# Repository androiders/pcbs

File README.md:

View this project on [CADLAB.io](https://cadlab.io/project/1457). 

# pcbs
Repo for pcb layouts, gerber and gcode files

## Ki-Cad

### PCB layout:
* Use as wide traces as possible. 1mm preffered.
* Dont use "filled areas" if possible. It does not make good geometry in flatcam
* Don't forget to set origin marker
* Export gerber: use auxiliary axis

## FlatCam

### geometry generation:
* If you are using thru-hole components or using bottom layer, mirror around y axis for both geometry and Drilling
* Edit drill files if necessary for fewer drill sizes
* TODO: test double sided layout by mirroring around center axis!

### Isolation generation:
* Current isolation mill depth to test: 0.04 mm (0.05 was tested and seems to work fine!) (Common copper depth is about 0.03 mm)
* Current feedrate on isolation milling to test: 60 mm/s
* spindle speed 12000 rpm

* use 0.2 mm tool width on cnc generation
* 2 passes with 0.1 overlap

### Cutout generation:
* Current cutout mill depth: 1.6 mm
* Current feedrate on cutout milling: 40 mm/s
* spindle speed 12000 rpm

### FlatCam defaults:
* put a link in ~/.FlatCAM/defaults.json

## bCNC

### Probe:
* Fastfeed: 120
* Probefeed: 25
* Probe points: 4/cm (in each direction)

### Drilling:
* Current drill plunge rate to test 20 mm/s
* spindle speed: 12000 rpm
* Drill depth: 1.6

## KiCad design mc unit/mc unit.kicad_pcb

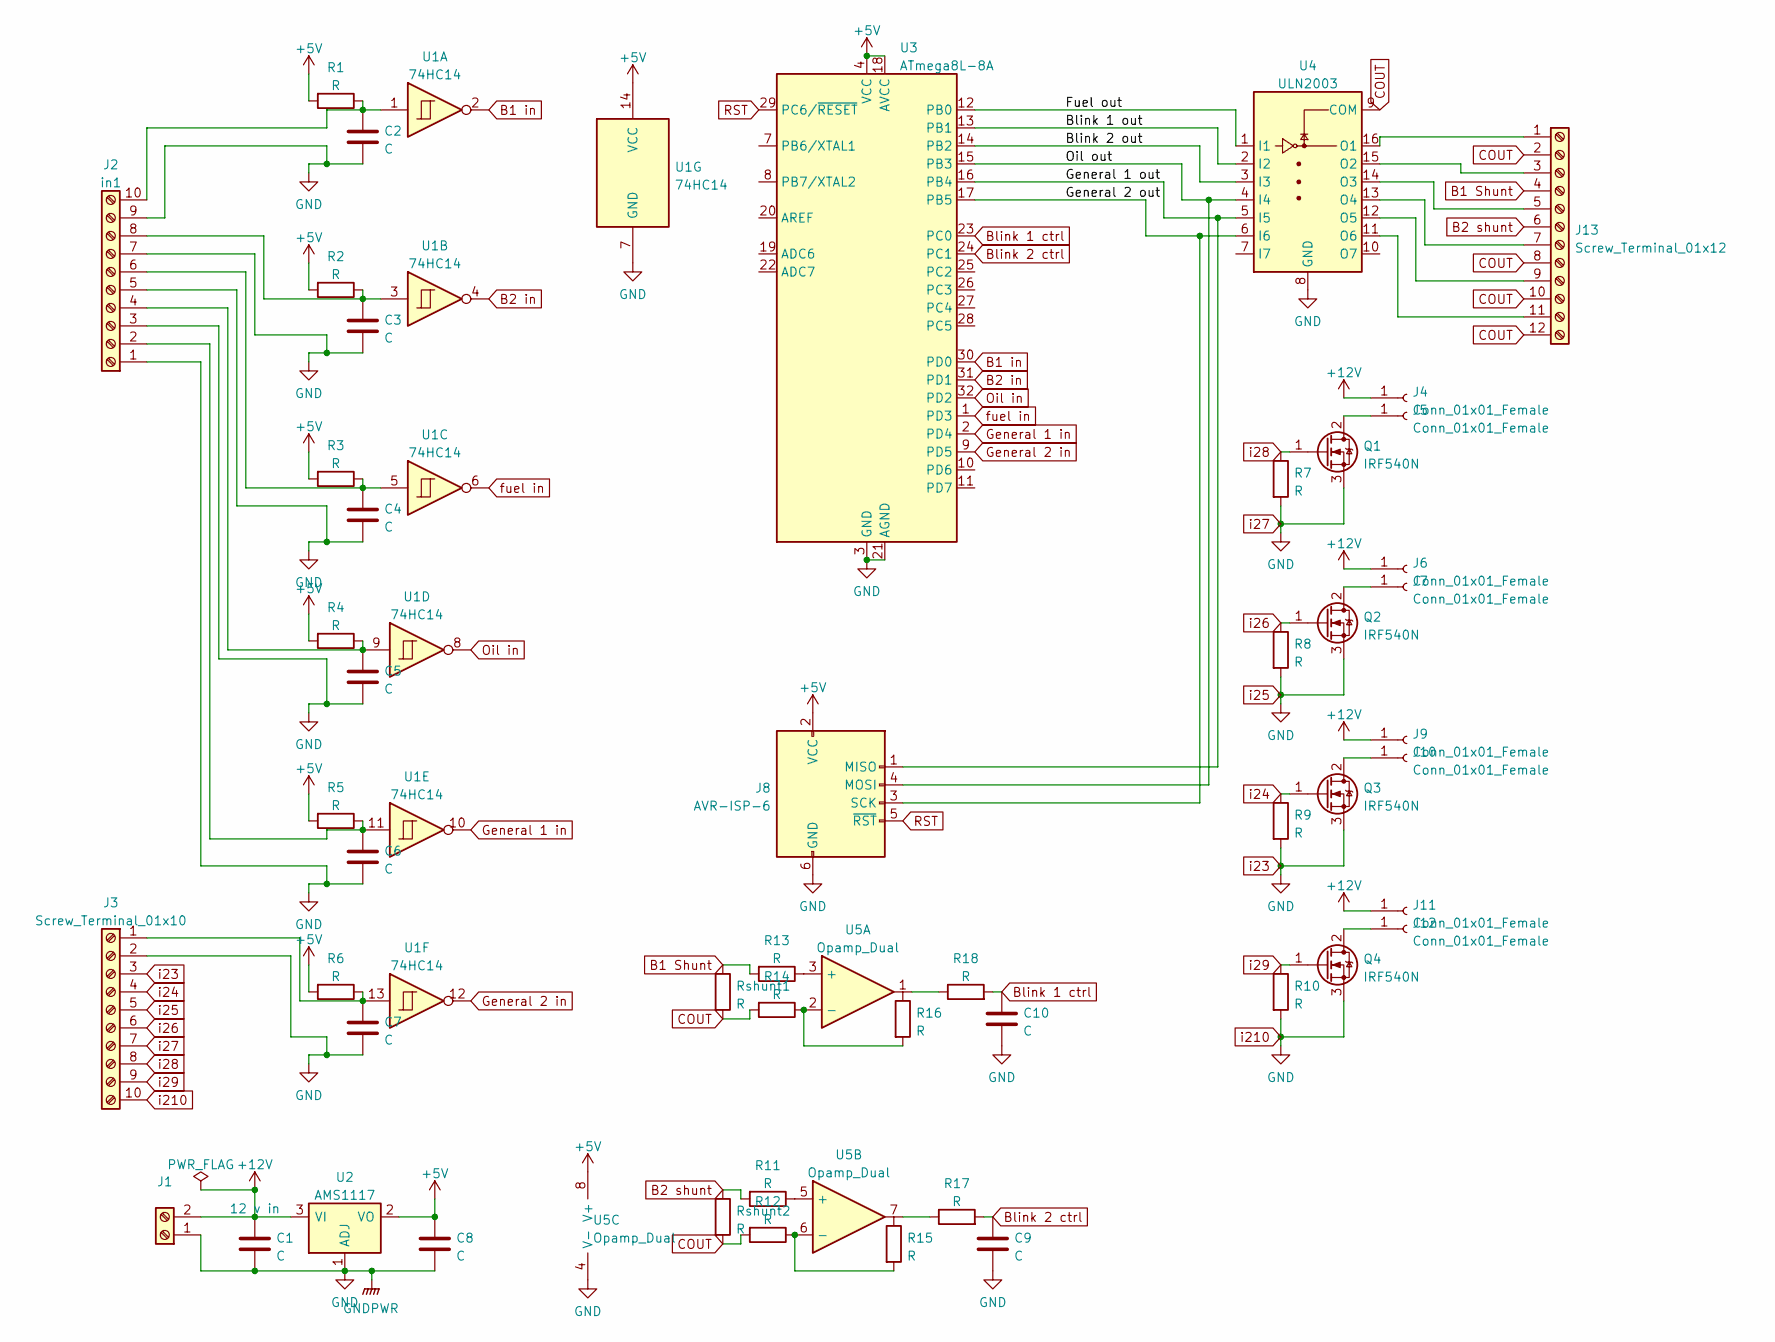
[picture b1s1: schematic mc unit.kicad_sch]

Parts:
C1, C2, C3, C4, C5, C6, C7, C8, C9, C10: C; C_1206_3216Metric
J1: 12 v in; TerminalBlock_Phoenix_MKDS-1,5-2-5.08_1x02_P5.08mm_Horizont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
J2: in1; TerminalBlock_Phoenix_MPT-0,5-10-2.54_1x10_P2.54mm_Horizont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
J3: Screw_Terminal_01x10; TerminalBlock_Phoenix_MPT-0,5-10-2.54_1x10_P2.54mm_Horizont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
J4, J5, J6, J7, J9, J10, J11, J12: Conn_01x01_Female; Pin_D1.0mm_L10.0mm_LooseFit
J8: AVR-ISP-6; IDC-Header_2x03_P2.54mm_Vertical
J13: Screw_Terminal_01x12; TerminalBlock_Phoenix_MPT-0,5-12-2.54_1x12_P2.54mm_Horizont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
Q1, Q2, Q3, Q4: IRF540N; TO-220-3_Vertical
R1, R2, R3, R4, R5, R6, R7, R8, R9, R10, R11, R12, R13, R14, R15, R16, R17, R18: R; R_1206_3216Metric
Rshunt1, Rshunt2: R; R_1206_3216Metric
U1: 74HC14; SO-14_5.3x10.2mm_P1.27mm
U2: AMS1117; SOT-223-3_TabPin2
U3: ATmega8L-8A; TQFP-32_7x7mm_P0.8mm
U4: ULN2003; SOIC-16_3.9x9.9mm_P1.27mm
U5: Opamp_Dual; SOIC-8_3.9x4.9mm_P1.27mm

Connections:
+5V: C8.1, J8.2 (VCC), R1.2, R2.2, R3.2, R4.2, R5.2, R6.2, U1.14 (VCC), U2.2 (VO), U3.4 (VCC), U3.6 (VCC), U3.18 (AVCC), U5.8 (V+)
+12V: C1.1, J1.2, J4.1, J6.1, J9.1, J11.1, U2.3 (VI)
/Blink 1 out: U3.13 (PB1), U4.2 (I2)
/Blink 2 out: U3.14 (PB2), U4.3 (I3)
/Fuel out: U3.12 (PB0), U4.1 (I1)
/General 1 out: J8.1 (MISO), U3.16 (PB4), U4.5 (I5)
/General 2 out: J8.3 (SCK), U3.17 (PB5), U4.6 (I6)
/Oil out: J8.4 (MOSI), U3.15 (PB3), U4.4 (I4)
B1 Shunt: J13.4, R13.2, Rshunt1.1
B1 in: U1.2, U3.30 (PD0)
B2 in: U1.4, U3.31 (PD1)
B2 shunt: J13.6, R11.2, Rshunt2.1
Blink 1 ctrl: C10.1, R18.2, U3.23 (PC0)
Blink 2 ctrl: C9.1, R17.2, U3.24 (PC1)
COUT: J13.2, J13.8, J13.10, J13.12, R12.2, R14.2, Rshunt1.2, Rshunt2.2, U4.9 (COM)
General 1 in: U1.10, U3.2 (PD4)
General 2 in: U1.12, U3.9 (PD5)
unnamed: C2.1, J2.10, R1.1, U1.1
unnamed: C3.1, J2.8, R2.1, U1.3
unnamed: C4.1, J2.6, R3.1, U1.5
unnamed: C5.1, J2.4, R4.1, U1.9
unnamed: C6.1, J2.2, R5.1, U1.11
unnamed: C7.1, J3.1, R6.1, U1.13
unnamed: J5.1, Q1.2 (D)
unnamed: J7.1, Q2.2 (D)
unnamed: J10.1, Q3.2 (D)
unnamed: J12.1, Q4.2 (D)
unnamed: R11.1, U5.5 (+)
unnamed: R12.1, R15.2, U5.6 (-)
unnamed: R13.1, U5.3 (+)
unnamed: R14.1, R16.2, U5.2 (-)
unnamed: R17.1, U5.7
unnamed: R18.1, U5.1
unnamed: J13.11, U4.11 (O6)
unnamed: J13.9, U4.12 (O5)
unnamed: J13.7, U4.13 (O4)
unnamed: J13.5, U4.14 (O3)
unnamed: J13.3, U4.15 (O2)
unnamed: J13.1, U4.16 (O1)
Oil in: U1.8, U3.32 (PD2)
RST: J8.5 (~RST), U3.29 (PC6/~RESET)
fuel in: U1.6, U3.1 (PD3)
i24: J3.4, Q3.1 (G), R9.1
i26: J3.6, Q2.1 (G), R8.1
i28: J3.8, Q1.1 (G), R7.1
i29: J3.9, Q4.1 (G), R10.1
i210: C1.2, C2.2, C3.2, C4.2, C5.2, C6.2, C7.2, C8.2, C9.2, C10.2, J1.1, J2.1, J2.3, J2.5, J2.7, J2.9, J3.2, J3.3, J3.5, J3.7, J3.10, J8.6 (GND), Q1.3 (S), Q2.3 (S), Q3.3 (S), Q4.3 (S), R7.2, R8.2, R9.2, R10.2, U1.7 (GND), U2.1 (ADJ), U3.3 (GND), U3.5 (GND), U3.21 (AGND), U4.8 (GND), U5.4 (V-)

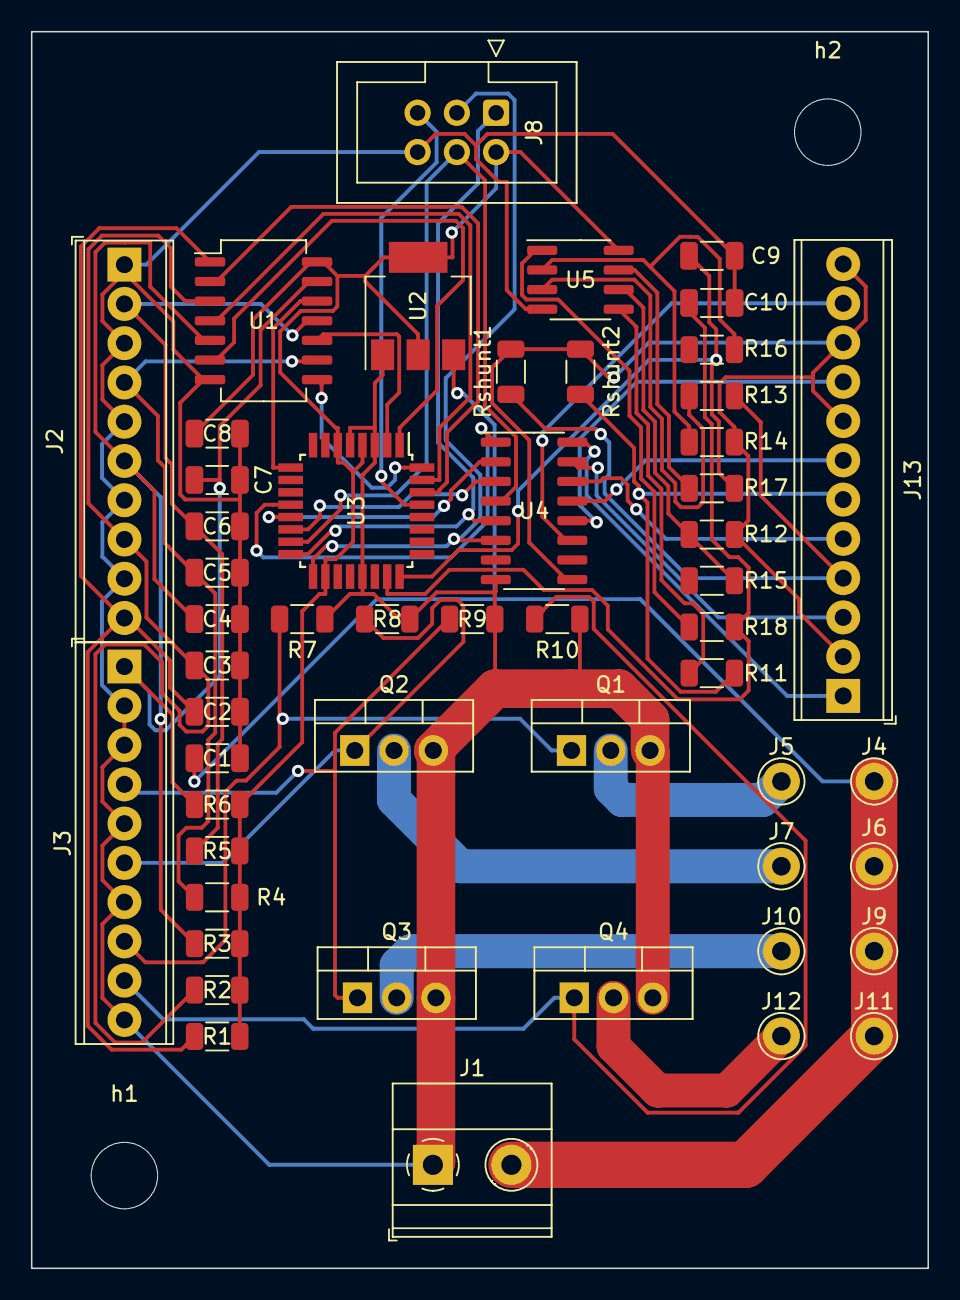
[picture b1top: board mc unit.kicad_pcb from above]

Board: 2 copper layers, 58.0 x 80.0 mm, 54 parts (0 on the bottom side), 47 nets.

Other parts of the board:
h1, h2: MountingHole_4.3mm_M4

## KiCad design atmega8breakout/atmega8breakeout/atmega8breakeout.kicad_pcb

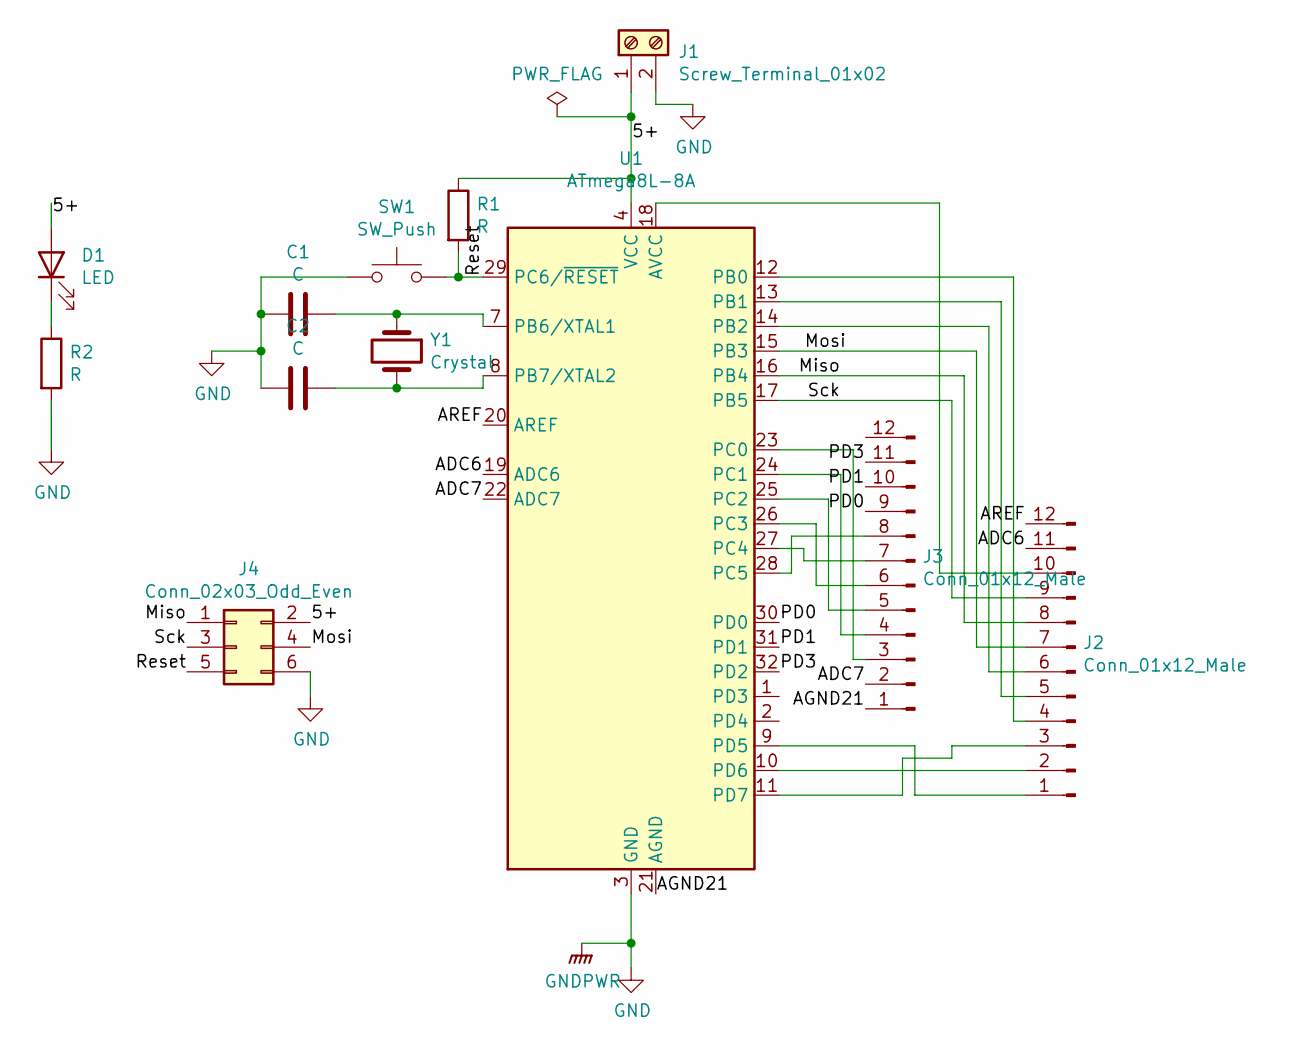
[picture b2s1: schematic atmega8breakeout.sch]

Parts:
C1, C2: C; C_0603_1608Metric
D1: LED; LED_0603_1608Metric
J1: Screw_Terminal_01x02; TerminalBlock_bornier-2_P5.08mm
J2, J3: Conn_01x12_Male; PinHeader_1x12_P2.54mm_Vertical
J4: Conn_02x03_Odd_Even; PinHeader_2x03_P2.00mm_Vertical
R1, R2: R; R_0603_1608Metric
SW1: SW_Push; SW_SPST_FSMSM
U1: ATmega8L-8A; TQFP-32_7x7mm_P0.8mm
Y1: Crystal; Crystal_HC49-U_Vertical

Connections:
/5+: D1.2 (A), J1.1, J4.2, R1.1, U1.4 (VCC), U1.6 (VCC)
/ADC6: J2.11, U1.19 (ADC6)
/ADC7: J3.2, U1.22 (ADC7)
/AGND21: J3.1, U1.21 (AGND)
/AREF: J2.12, U1.20 (AREF)
/Miso: J2.8, J4.1, U1.16 (PB4)
/Mosi: J2.7, J4.4, U1.15 (PB3)
/PD0: J3.9, U1.30 (PD0)
/PD1: J3.10, U1.31 (PD1)
/PD3: J3.11, U1.32 (PD2)
/Reset: J4.5, R1.2, SW1.2, U1.29 (PC6/~RESET)
/Sck: J2.9, J4.3, U1.17 (PB5)
GND: C1.2, C2.2, J1.2, J4.6, R2.2, SW1.1, U1.3 (GND), U1.5 (GND)
unnamed: C1.1, U1.7 (PB6/XTAL1), Y1.1
unnamed: C2.1, U1.8 (PB7/XTAL2), Y1.2
unnamed: D1.1 (K), R2.1
unnamed: J2.1, U1.9 (PD5)
unnamed: J2.2, U1.10 (PD6)
unnamed: J2.3, U1.11 (PD7)
unnamed: J2.4, U1.12 (PB0)
unnamed: J2.5, U1.13 (PB1)
unnamed: J2.6, U1.14 (PB2)
unnamed: J2.10, U1.18 (AVCC)
unnamed: J3.3, U1.23 (PC0)
unnamed: J3.4, U1.24 (PC1)
unnamed: J3.5, U1.25 (PC2)
unnamed: J3.6, U1.26 (PC3)
unnamed: J3.7, U1.27 (PC4)
unnamed: J3.8, U1.28 (PC5)

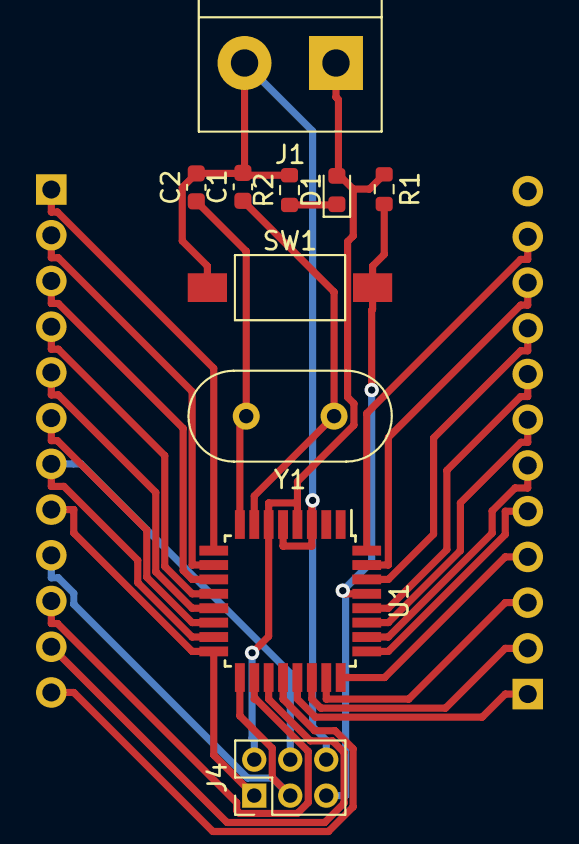
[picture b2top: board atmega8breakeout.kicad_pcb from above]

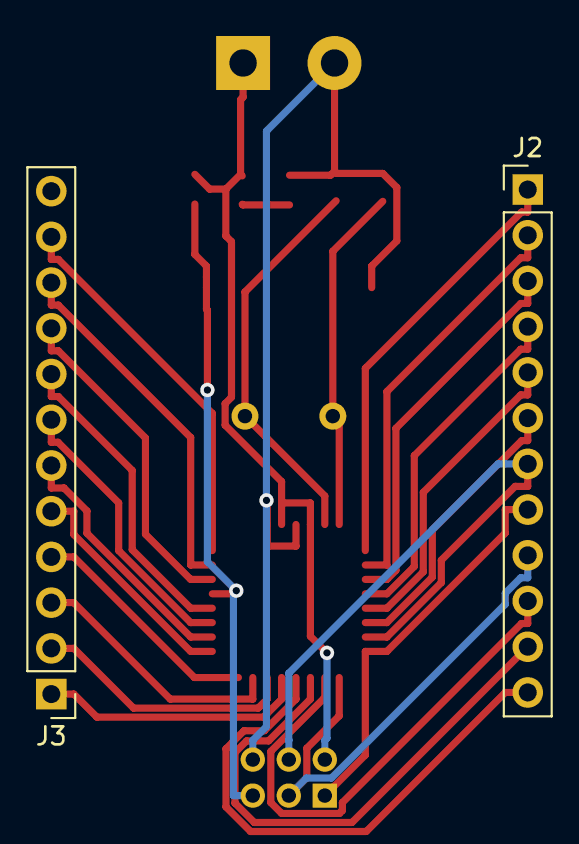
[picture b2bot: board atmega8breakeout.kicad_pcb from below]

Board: 2 copper layers, 12 parts (2 on the bottom side), 29 nets.

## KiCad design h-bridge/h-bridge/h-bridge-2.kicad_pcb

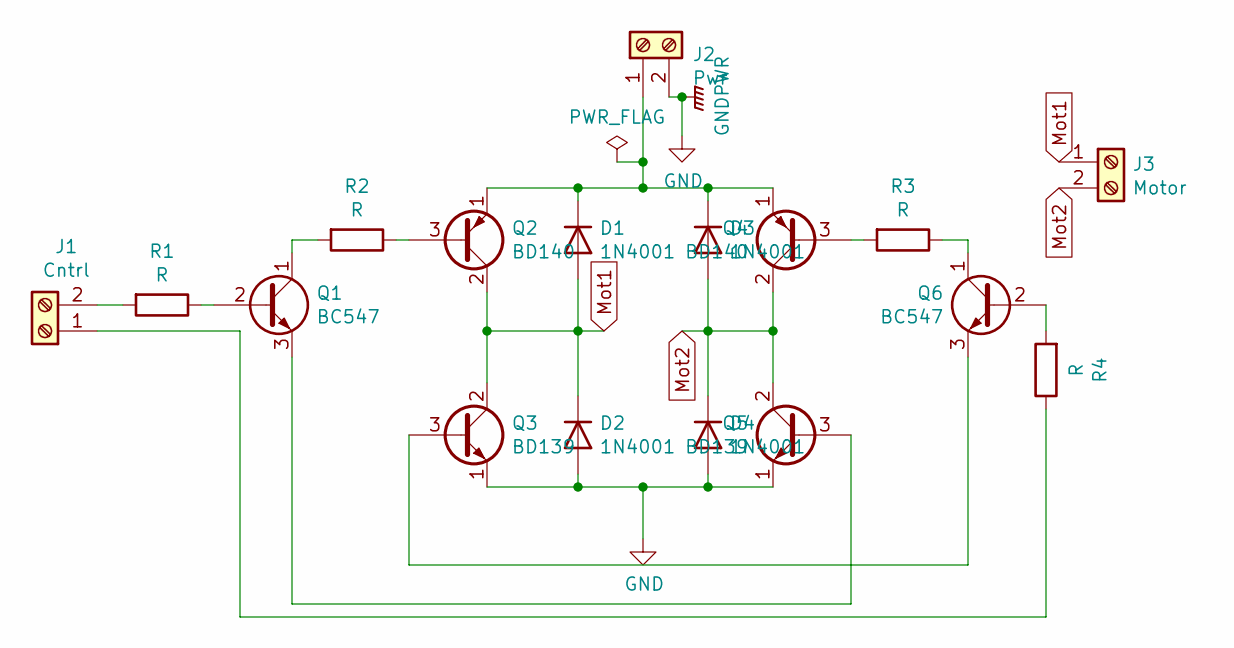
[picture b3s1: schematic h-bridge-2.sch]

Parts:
D1, D2, D3, D4: 1N4001; D_DO-41_SOD81_P10.16mm_Horizontal
J1: Cntrl; TerminalBlock_Phoenix_MKDS-3-2-5.08_1x02_P5.08mm_Horizontal
J2: Pwr; TerminalBlock_Phoenix_MKDS-3-2-5.08_1x02_P5.08mm_Horizontal
J3: Motor; TerminalBlock_Phoenix_MKDS-3-2-5.08_1x02_P5.08mm_Horizontal
Q1, Q6: BC547; TO-92_Inline
Q2, Q4: BD140; TO-126-3_Vertical
Q3, Q5: BD139; TO-126-3_Vertical
R1, R2, R3, R4: R; R_Axial_DIN0207_L6.3mm_D2.5mm_P7.62mm_Horizontal

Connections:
GND: D2.2 (A), D4.2 (A), J2.2, Q3.1 (E), Q5.1 (E)
Mot1: D1.2 (A), D2.1 (K), J3.1, Q2.2 (C), Q3.2 (C)
Mot2: D3.2 (A), D4.1 (K), J3.2, Q4.2 (C), Q5.2 (C)
unnamed: D1.1 (K), D3.1 (K), J2.1, Q2.1 (E), Q4.1 (E)
unnamed: J1.1, R4.1
unnamed: J1.2, R1.2
unnamed: Q1.1 (C), R2.2
unnamed: Q1.2 (B), R1.1
unnamed: Q1.3 (E), Q5.3 (B)
unnamed: Q2.3 (B), R2.1
unnamed: Q3.3 (B), Q6.3 (E)
unnamed: Q4.3 (B), R3.2
unnamed: Q6.1 (C), R3.1
unnamed: Q6.2 (B), R4.2

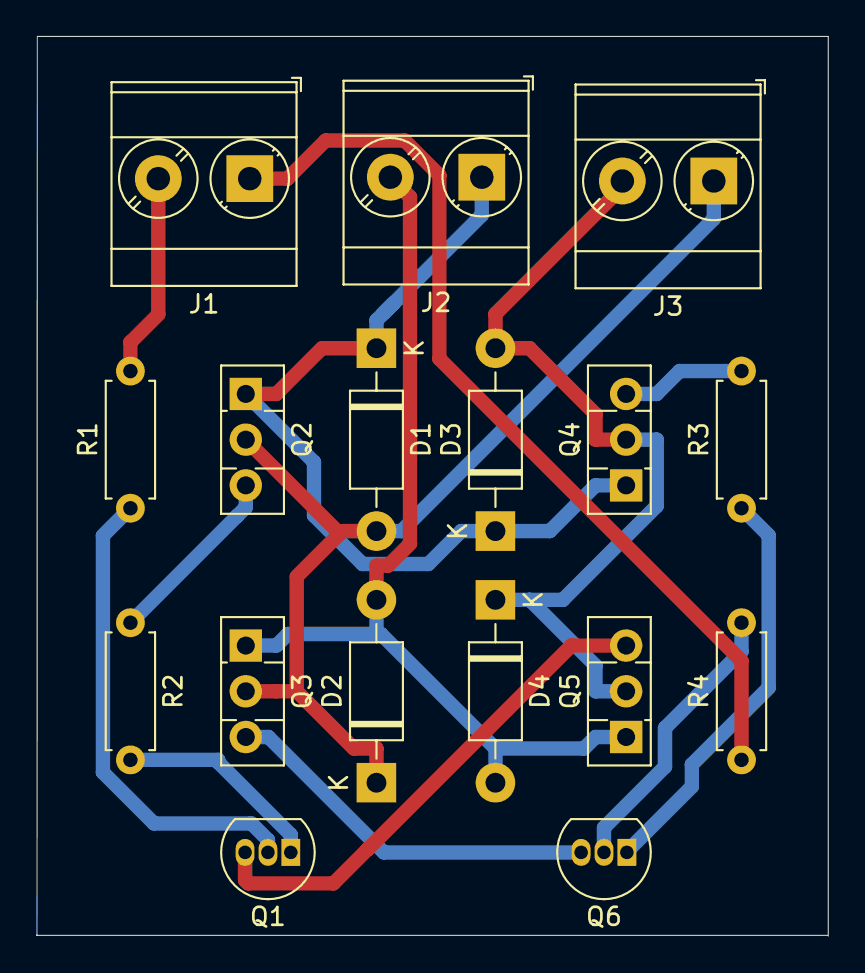
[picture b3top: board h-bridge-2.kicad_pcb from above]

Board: 2 copper layers, 44.0 x 50.0 mm, 17 parts (0 on the bottom side), 14 nets.

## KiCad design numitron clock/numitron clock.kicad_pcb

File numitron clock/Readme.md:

TODO:
* ~~Fixa banorna~~
* ~~Fixa annotations~~
    * ~~labels i komponenter~~
    * ~~rätt nummer~~
    * ~~mera logisk ordning~~
* Rotera D2 o D2 - dont do
* ~~ordning på r1,r2,r3~~
* värden (resistans) samma på r1,r2,r3? - no
* ~~Rotera numitron rör 180 grader~~
* ta bort j2?

Bonus: Göra SMD version av PCB

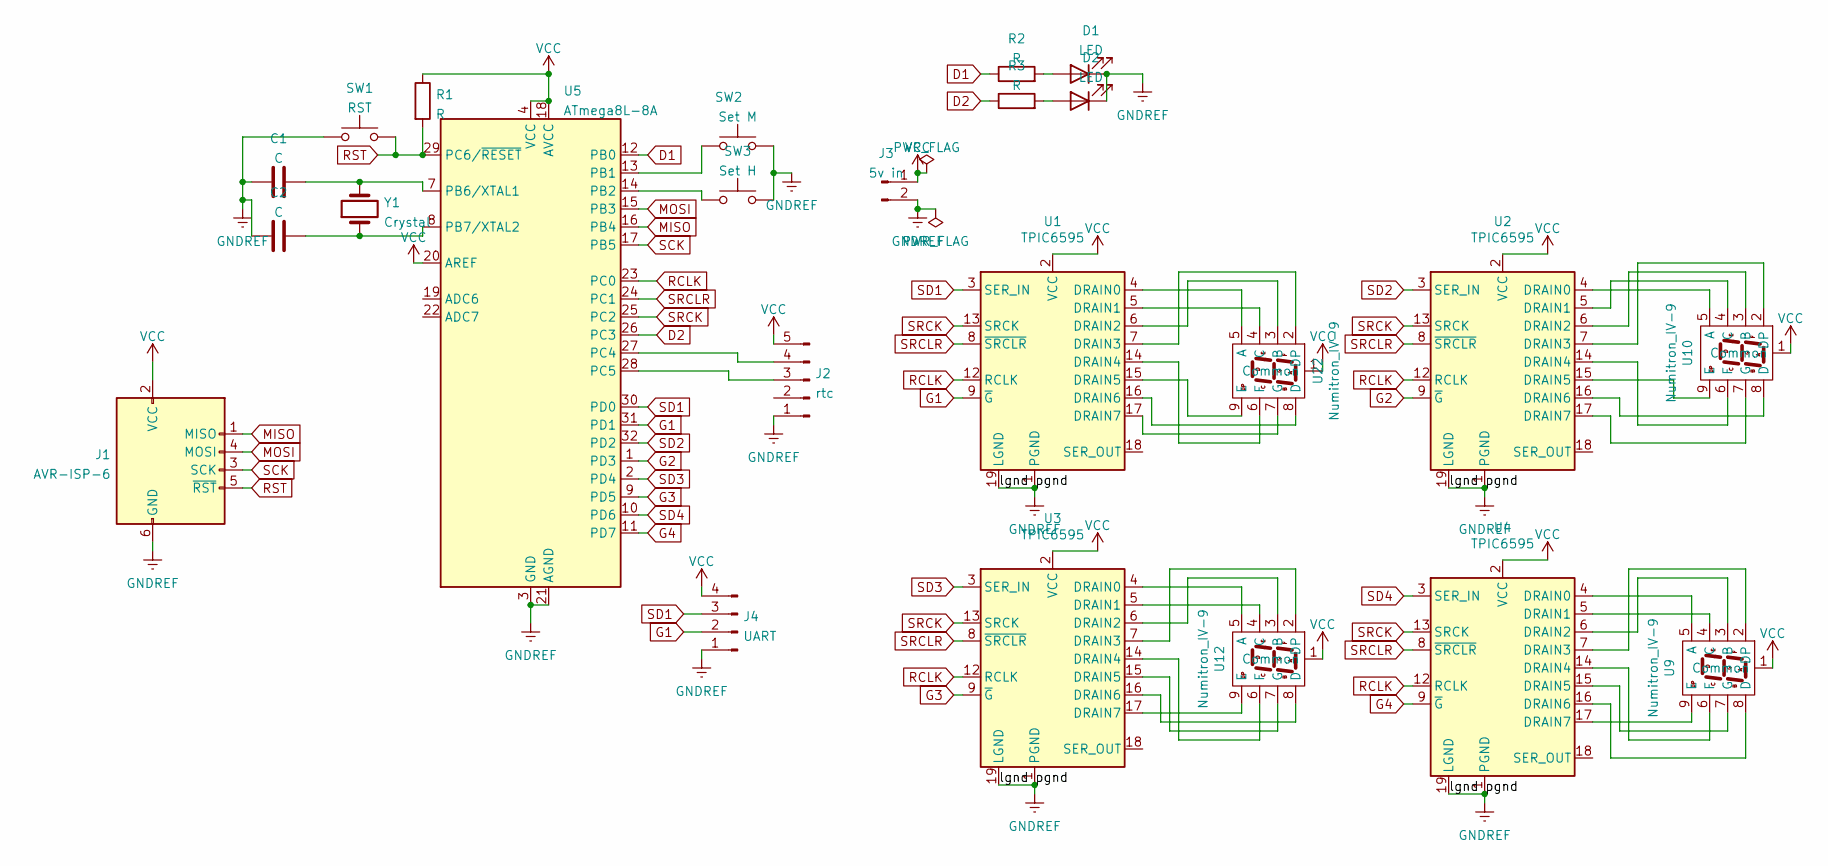
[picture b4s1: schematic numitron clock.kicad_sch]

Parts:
C1, C2: C; C_Disc_D3.8mm_W2.6mm_P2.50mm
D1, D2: LED; LED_D5.0mm
J1: AVR-ISP-6; IDC-Header_2x03_P2.54mm_Vertical
J2: rtc; PinHeader_1x05_P2.54mm_Vertical
J3: 5v in; TerminalBlock_Phoenix_MKDS-1,5-2-5.08_1x02_P5.08mm_Horizont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
J4: UART; PinHeader_1x04_P2.54mm_Vertical
R1, R2, R3: R; R_Axial_DIN0207_L6.3mm_D2.5mm_P7.62mm_Horizontal
SW1: RST; SW_SPST_CK_RS282G05A3
SW2: Set M; SW_SPST_CK_RS282G05A3
SW3: Set H; SW_SPST_CK_RS282G05A3
U1, U2, U3, U4: TPIC6595; DIP-20_W7.62mm_LongPads
U5: ATmega8L-8A; TQFP-32_7x7mm_P0.8mm
U9, U10, U12, U22: Numitron_IV-9; numitron iv-9
Y1: Crystal; Crystal_Round_D1.5mm_Vertical

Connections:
D1: R2.1, U5.12 (PB0)
D2: R3.1, U5.26 (PC3)
G1: J4.2, U1.9 (~G), U5.31 (PD1)
G2: U2.9 (~G), U5.1 (PD3)
G3: U3.9 (~G), U5.9 (PD5)
G4: U4.9 (~G), U5.11 (PD7)
GNDREF: C1.1, C2.1, D1.1 (K), D2.1 (K), J1.6 (GND), J2.1, J3.2, J4.1, SW1.1, SW2.2, SW3.2, U1.1 (PGND), U1.10 (PGND), U1.11 (PGND), U1.19 (LGND), U1.20 (PGND), U2.1 (PGND), U2.10 (PGND), U2.11 (PGND), U2.19 (LGND), U2.20 (PGND), U3.1 (PGND), U3.10 (PGND), U3.11 (PGND), U3.19 (LGND), U3.20 (PGND), U4.1 (PGND), U4.10 (PGND), U4.11 (PGND), U4.19 (LGND), U4.20 (PGND), U5.3 (GND), U5.5 (GND), U5.21 (AGND)
MISO: J1.1 (MISO), U5.16 (PB4)
MOSI: J1.4 (MOSI), U5.15 (PB3)
unnamed: C1.2, U5.7 (PB6/XTAL1), Y1.2
unnamed: C2.2, U5.8 (PB7/XTAL2), Y1.1
unnamed: D1.2 (A), R2.2
unnamed: D2.2 (A), R3.2
unnamed: J2.3, U5.28 (PC5)
unnamed: J2.4, U5.27 (PC4)
unnamed: SW2.1, U5.13 (PB1)
unnamed: SW3.1, U5.14 (PB2)
unnamed: U1.4 (DRAIN0), U22.5 (A)
unnamed: U1.5 (DRAIN1), U22.4 (C)
unnamed: U1.6 (DRAIN2), U22.3 (B)
unnamed: U1.7 (DRAIN3), U22.2 (DP)
unnamed: U1.14 (DRAIN4), U22.6 (F)
unnamed: U1.16 (DRAIN6), U22.8 (D)
unnamed: U1.17 (DRAIN7), U22.7 (G)
unnamed: U4.4 (DRAIN0), U9.5 (A)
unnamed: U4.5 (DRAIN1), U9.4 (C)
unnamed: U4.6 (DRAIN2), U9.3 (B)
unnamed: U4.7 (DRAIN3), U9.2 (DP)
unnamed: U4.14 (DRAIN4), U9.6 (F)
unnamed: U4.15 (DRAIN5), U9.7 (G)
unnamed: U4.16 (DRAIN6), U9.8 (D)
unnamed: U4.17 (DRAIN7), U9.9 (E)
unnamed: U2.7 (DRAIN3), U10.2 (DP)
unnamed: U2.6 (DRAIN2), U10.3 (B)
unnamed: U2.5 (DRAIN1), U10.4 (C)
unnamed: U2.4 (DRAIN0), U10.5 (A)
unnamed: U2.14 (DRAIN4), U10.6 (F)
unnamed: U2.17 (DRAIN7), U10.7 (G)
unnamed: U2.16 (DRAIN6), U10.8 (D)
unnamed: U2.15 (DRAIN5), U10.9 (E)
unnamed: U3.7 (DRAIN3), U12.2 (DP)
unnamed: U3.6 (DRAIN2), U12.3 (B)
unnamed: U3.5 (DRAIN1), U12.4 (C)
unnamed: U3.4 (DRAIN0), U12.5 (A)
unnamed: U3.14 (DRAIN4), U12.6 (F)
unnamed: U3.15 (DRAIN5), U12.7 (G)
unnamed: U3.16 (DRAIN6), U12.8 (D)
unnamed: U3.17 (DRAIN7), U12.9 (E)
unnamed: U1.15 (DRAIN5), U22.9 (E)
RCLK: U1.12 (RCLK), U2.12 (RCLK), U3.12 (RCLK), U4.12 (RCLK), U5.23 (PC0)
RST: J1.5 (~RST), R1.2, SW1.2, U5.29 (PC6/~RESET)
SCK: J1.3 (SCK), U5.17 (PB5)
SD1: J4.3, U1.3 (SER_IN), U5.30 (PD0)
SD2: U2.3 (SER_IN), U5.32 (PD2)
SD3: U3.3 (SER_IN), U5.2 (PD4)
SD4: U4.3 (SER_IN), U5.10 (PD6)
SRCK: U1.13 (SRCK), U2.13 (SRCK), U3.13 (SRCK), U4.13 (SRCK), U5.25 (PC2)
SRCLR: U1.8 (~SRCLR), U2.8 (~SRCLR), U3.8 (~SRCLR), U4.8 (~SRCLR), U5.24 (PC1)
VCC: J1.2 (VCC), J2.5, J3.1, J4.4, R1.1, U1.2 (VCC), U2.2 (VCC), U3.2 (VCC), U4.2 (VCC), U5.4 (VCC), U5.6 (VCC), U5.18 (AVCC), U5.20 (AREF), U9.1 (Common), U10.1 (Common), U12.1 (Common), U22.1 (Common)

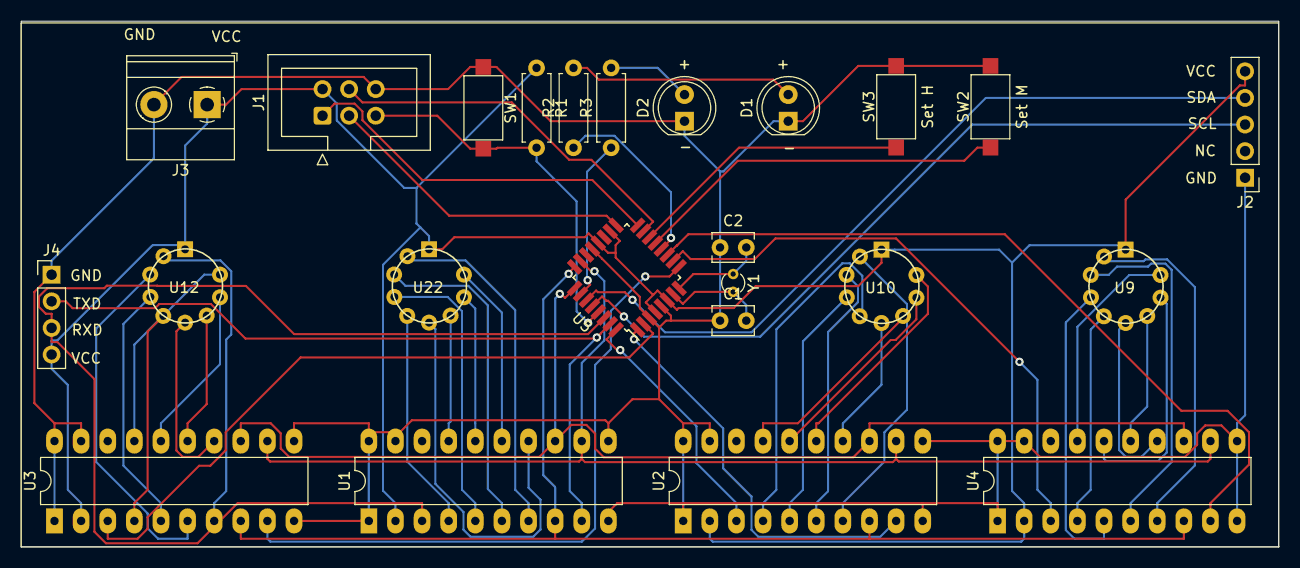
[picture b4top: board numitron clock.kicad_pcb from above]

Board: 2 copper layers, 120.0 x 50.2 mm, 24 parts (0 on the bottom side), 59 nets.

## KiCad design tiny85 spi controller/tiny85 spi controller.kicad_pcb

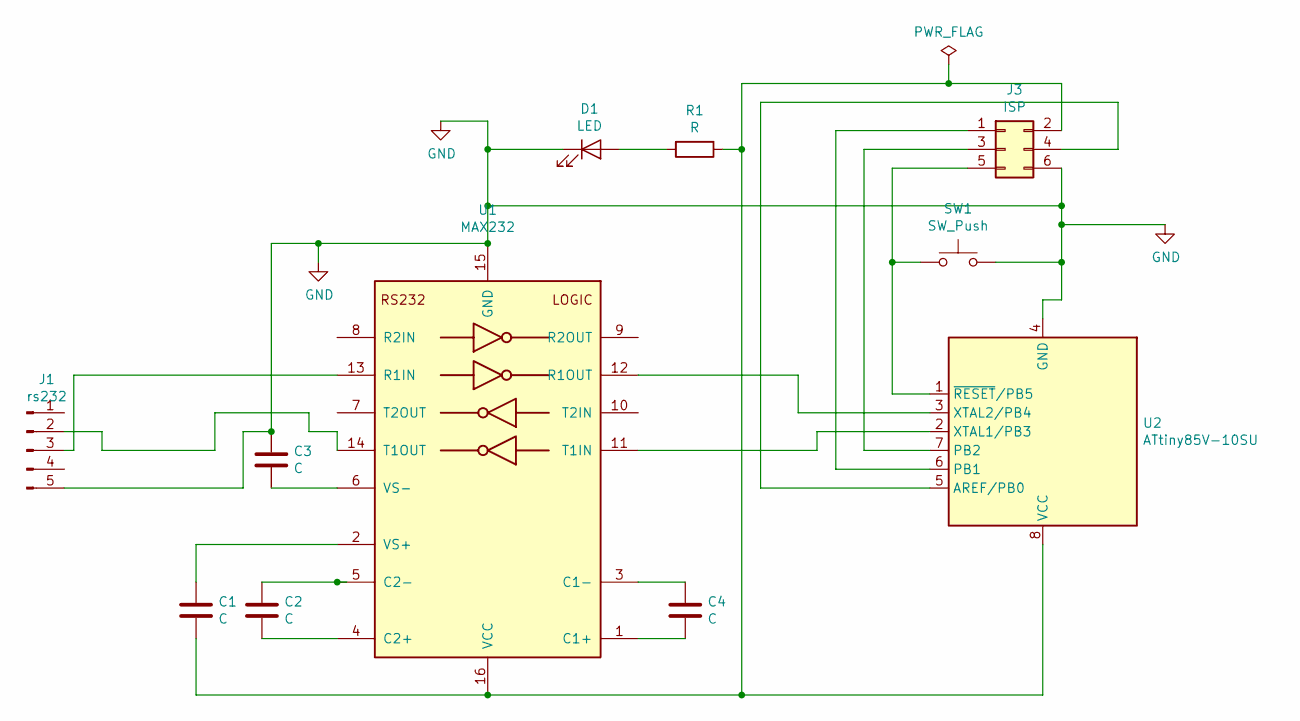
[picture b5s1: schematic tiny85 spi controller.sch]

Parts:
C1, C2, C3, C4: C; C_0603_1608Metric
D1: LED; LED_0402_1005Metric
J1: rs232; Harwin_M20-89005xx_1x05_P2.54mm_Horizontal
J3: ISP; PinSocket_2x03_P2.54mm_Vertical
R1: R; R_0201_0603Metric
SW1: SW_Push; SW_SPST_CK_RS282G05A3
U1: MAX232; SOIC-16W_7.5x10.3mm_P1.27mm
U2: ATtiny85V-10SU; SOIJ-8_5.3x5.3mm_P1.27mm

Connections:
GND: C3.1, D1.1 (K), J1.5, J3.6, SW1.2, U1.15 (GND), U2.4 (GND)
unnamed: C1.1, U1.2 (VS+)
unnamed: C1.2, J3.2, R1.1, U1.16 (VCC), U2.8 (VCC)
unnamed: C2.1, U1.5 (C2-)
unnamed: C2.2, U1.4 (C2+)
unnamed: C3.2, U1.6 (VS-)
unnamed: C4.1, U1.3 (C1-)
unnamed: C4.2, U1.1 (C1+)
unnamed: D1.2 (A), R1.2
unnamed: J1.2, U1.14 (T1OUT)
unnamed: J1.3, U1.13 (R1IN)
unnamed: J3.1, U2.6 (PB1)
unnamed: J3.3, U2.7 (PB2)
unnamed: J3.4, U2.5 (AREF/PB0)
unnamed: J3.5, SW1.1, U2.1 (~RESET~/PB5)
unnamed: U1.11 (T1IN), U2.2 (XTAL1/PB3)
unnamed: U1.12 (R1OUT), U2.3 (XTAL2/PB4)

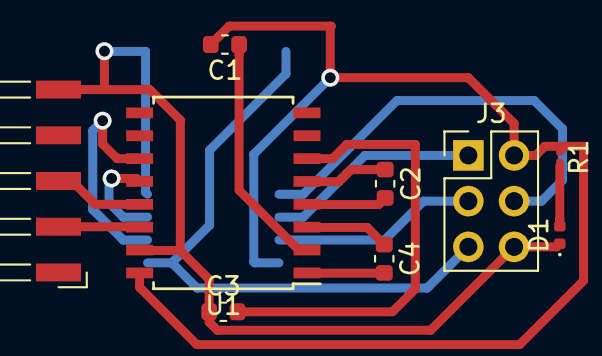
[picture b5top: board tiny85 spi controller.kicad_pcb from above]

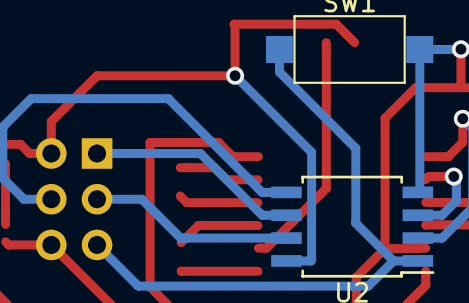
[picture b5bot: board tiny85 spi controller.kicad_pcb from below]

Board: 2 copper layers, 11 parts (2 on the bottom side), 17 nets.

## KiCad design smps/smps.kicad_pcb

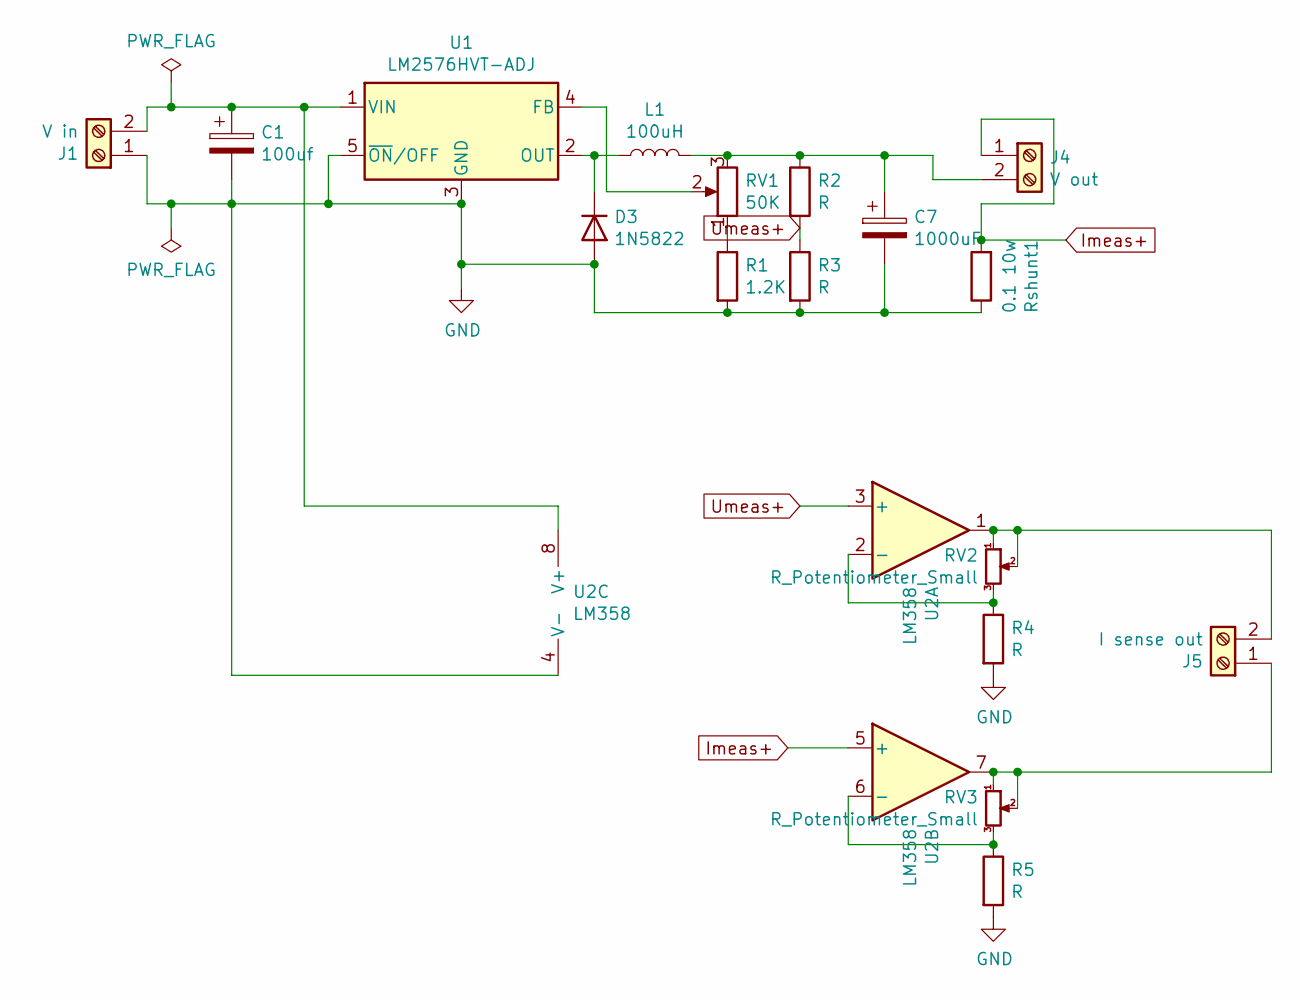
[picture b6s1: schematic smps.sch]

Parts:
C1: 100uf; CP_Radial_D10.0mm_P7.50mm
C7: 1000uF; CP_Radial_D10.0mm_P7.50mm
D3: 1N5822; D_DO-201AD_P12.70mm_Horizontal
J1: V in; TerminalBlock_Phoenix_MKDS-1,5-2-5.08_1x02_P5.08mm_Horizont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
J4: V out; TerminalBlock_Phoenix_MKDS-1,5-2-5.08_1x02_P5.08mm_Horizont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
J5: I sense out; TerminalBlock_Phoenix_MKDS-1,5-2-5.08_1x02_P5.08mm_Horizont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
L1: 100uH; L_Toroid_Vertical_L31.8mm_W15.9mm_P13.50mm_Bourns_5700
R1: 1.2K; R_Axial_DIN0207_L6.3mm_D2.5mm_P10.16mm_Horizontal
R2, R3, R4, R5: R; R_Axial_DIN0207_L6.3mm_D2.5mm_P10.16mm_Horizontal
RV1: 50K; TerminalBlock_Phoenix_MKDS-1,5-3-5.08_1x03_P5.08mm_Horizont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
RV2, RV3: R_Potentiometer_Small; Potentiometer_ACP_CA9-H3,8_Horizontal
Rshunt1: 0.1 10w; R_Axial_Power_L20.0mm_W6.4mm_P25.40mm
U1: LM2576HVT-ADJ; TO-220-5_P3.4x3.7mm_StaggerOdd_Lead3.8mm_Vertical
U2: LM358; DIP-8_W7.62mm_Socket

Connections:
GND: C1.2, C7.2, D3.2 (A), J1.1, R1.2, R3.2, R4.2, R5.2, Rshunt1.1, U1.3 (GND), U1.5 (~ON~/OFF), U2.4 (V-)
Imeas+: J4.1, Rshunt1.2, U2.5 (+)
unnamed: C1.1, J1.2, U1.1 (VIN), U2.8 (V+)
unnamed: C7.1, J4.2, L1.2, R2.1, RV1.3
unnamed: D3.1 (K), L1.1, U1.2 (OUT)
unnamed: J5.1, RV3.1, RV3.2, U2.7
unnamed: J5.2, RV2.1, RV2.2, U2.1
unnamed: R1.1, RV1.1
unnamed: R4.1, RV2.3, U2.2 (-)
unnamed: R5.1, RV3.3, U2.6 (-)
unnamed: RV1.2, U1.4 (FB)
Umeas+: R2.2, R3.1, U2.3 (+)

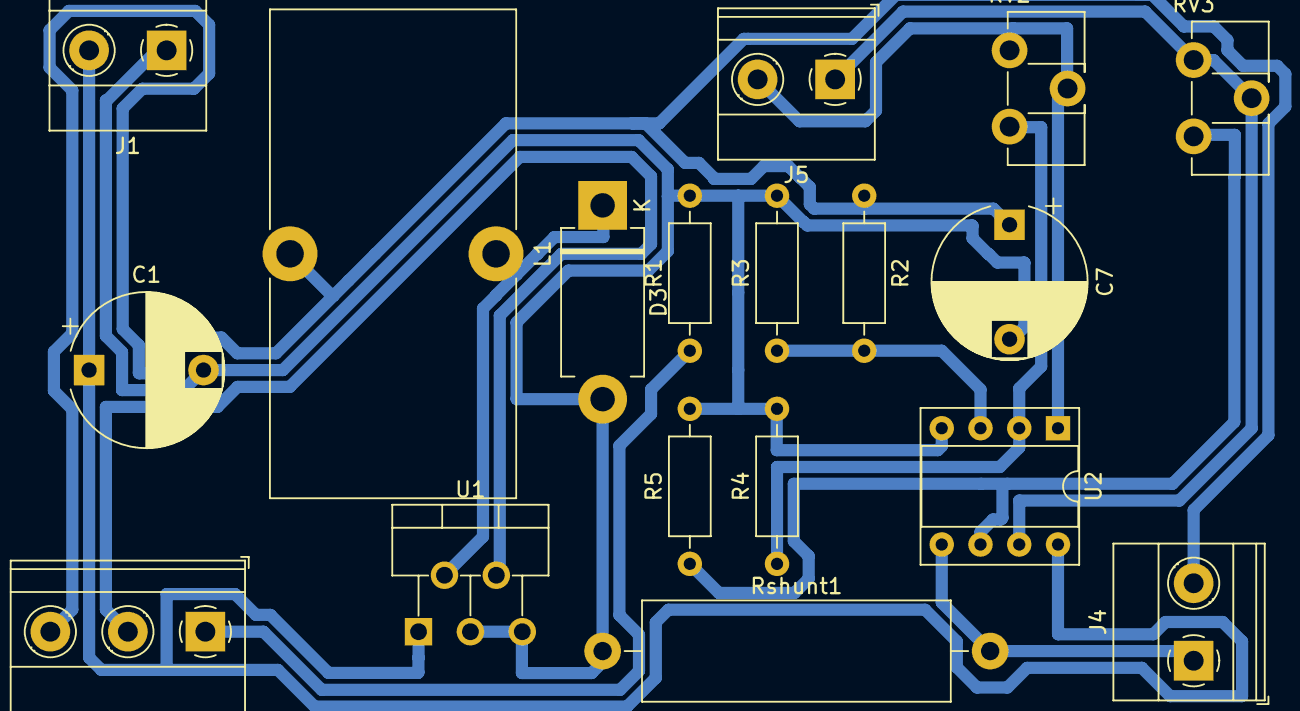
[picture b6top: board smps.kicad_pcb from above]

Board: 2 copper layers, 18 parts (0 on the bottom side), 12 nets.

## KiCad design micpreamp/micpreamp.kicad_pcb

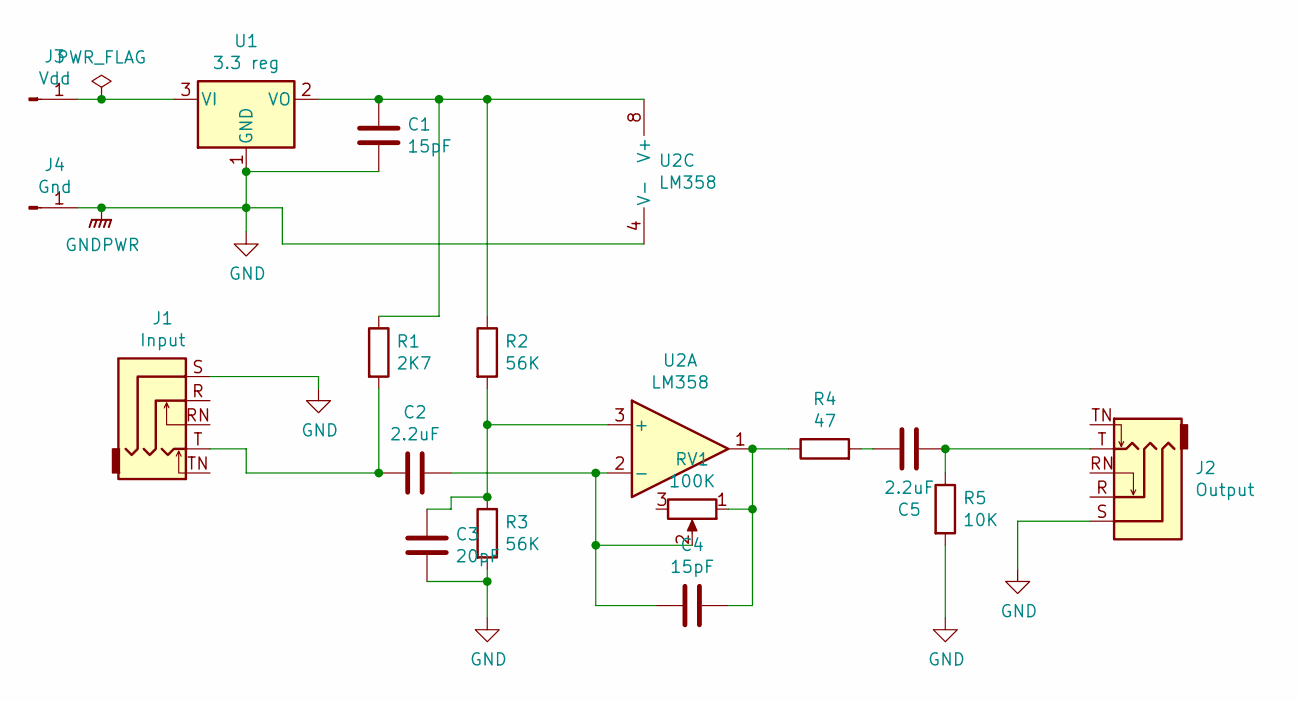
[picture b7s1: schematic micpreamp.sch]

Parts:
C1, C4: 15pF; C_Radial_D5.0mm_H5.0mm_P2.00mm
C2, C5: 2.2uF; C_Radial_D5.0mm_H5.0mm_P2.00mm
C3: 20pF; C_Radial_D5.0mm_H5.0mm_P2.00mm
J1: Input; StereoJack_3.5mm_Switch_Ledino_KB3SPRS_Horizontal
J2: Output; StereoJack_3.5mm_Switch_Ledino_KB3SPRS_Horizontal
J3: Vdd; Pin_D1.0mm_L10.0mm
J4: Gnd; Pin_D1.0mm_L10.0mm
R1: 2K7; R_Axial_DIN0207_L6.3mm_D2.5mm_P7.62mm_Horizontal
R2, R3: 56K; R_Axial_DIN0207_L6.3mm_D2.5mm_P7.62mm_Horizontal
R4: 47; R_Axial_DIN0207_L6.3mm_D2.5mm_P7.62mm_Horizontal
R5: 10K; R_Axial_DIN0207_L6.3mm_D2.5mm_P7.62mm_Horizontal
RV1: 100K; Potentiometer_Alps_RK09K_Single_Vertical
U1: 3.3 reg; TO-220-3_Vertical
U2: LM358; DIP-8_W7.62mm_LongPads

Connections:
GND: C1.2, C3.1, J1.S, J2.S, J4.1, R3.2, R5.2, U1.1 (GND), U2.4 (V-)
unnamed: C1.1, R1.1, R2.1, U1.2 (VO), U2.8 (V+)
unnamed: C2.1, C4.2, RV1.2, U2.2 (-)
unnamed: C2.2, J1.T, R1.2
unnamed: C3.2, R2.2, R3.1, U2.3 (+)
unnamed: C4.1, R4.1, RV1.1, U2.1
unnamed: C5.1, R4.2
unnamed: C5.2, J2.T, R5.1
unnamed: J3.1, U1.3 (VI)
